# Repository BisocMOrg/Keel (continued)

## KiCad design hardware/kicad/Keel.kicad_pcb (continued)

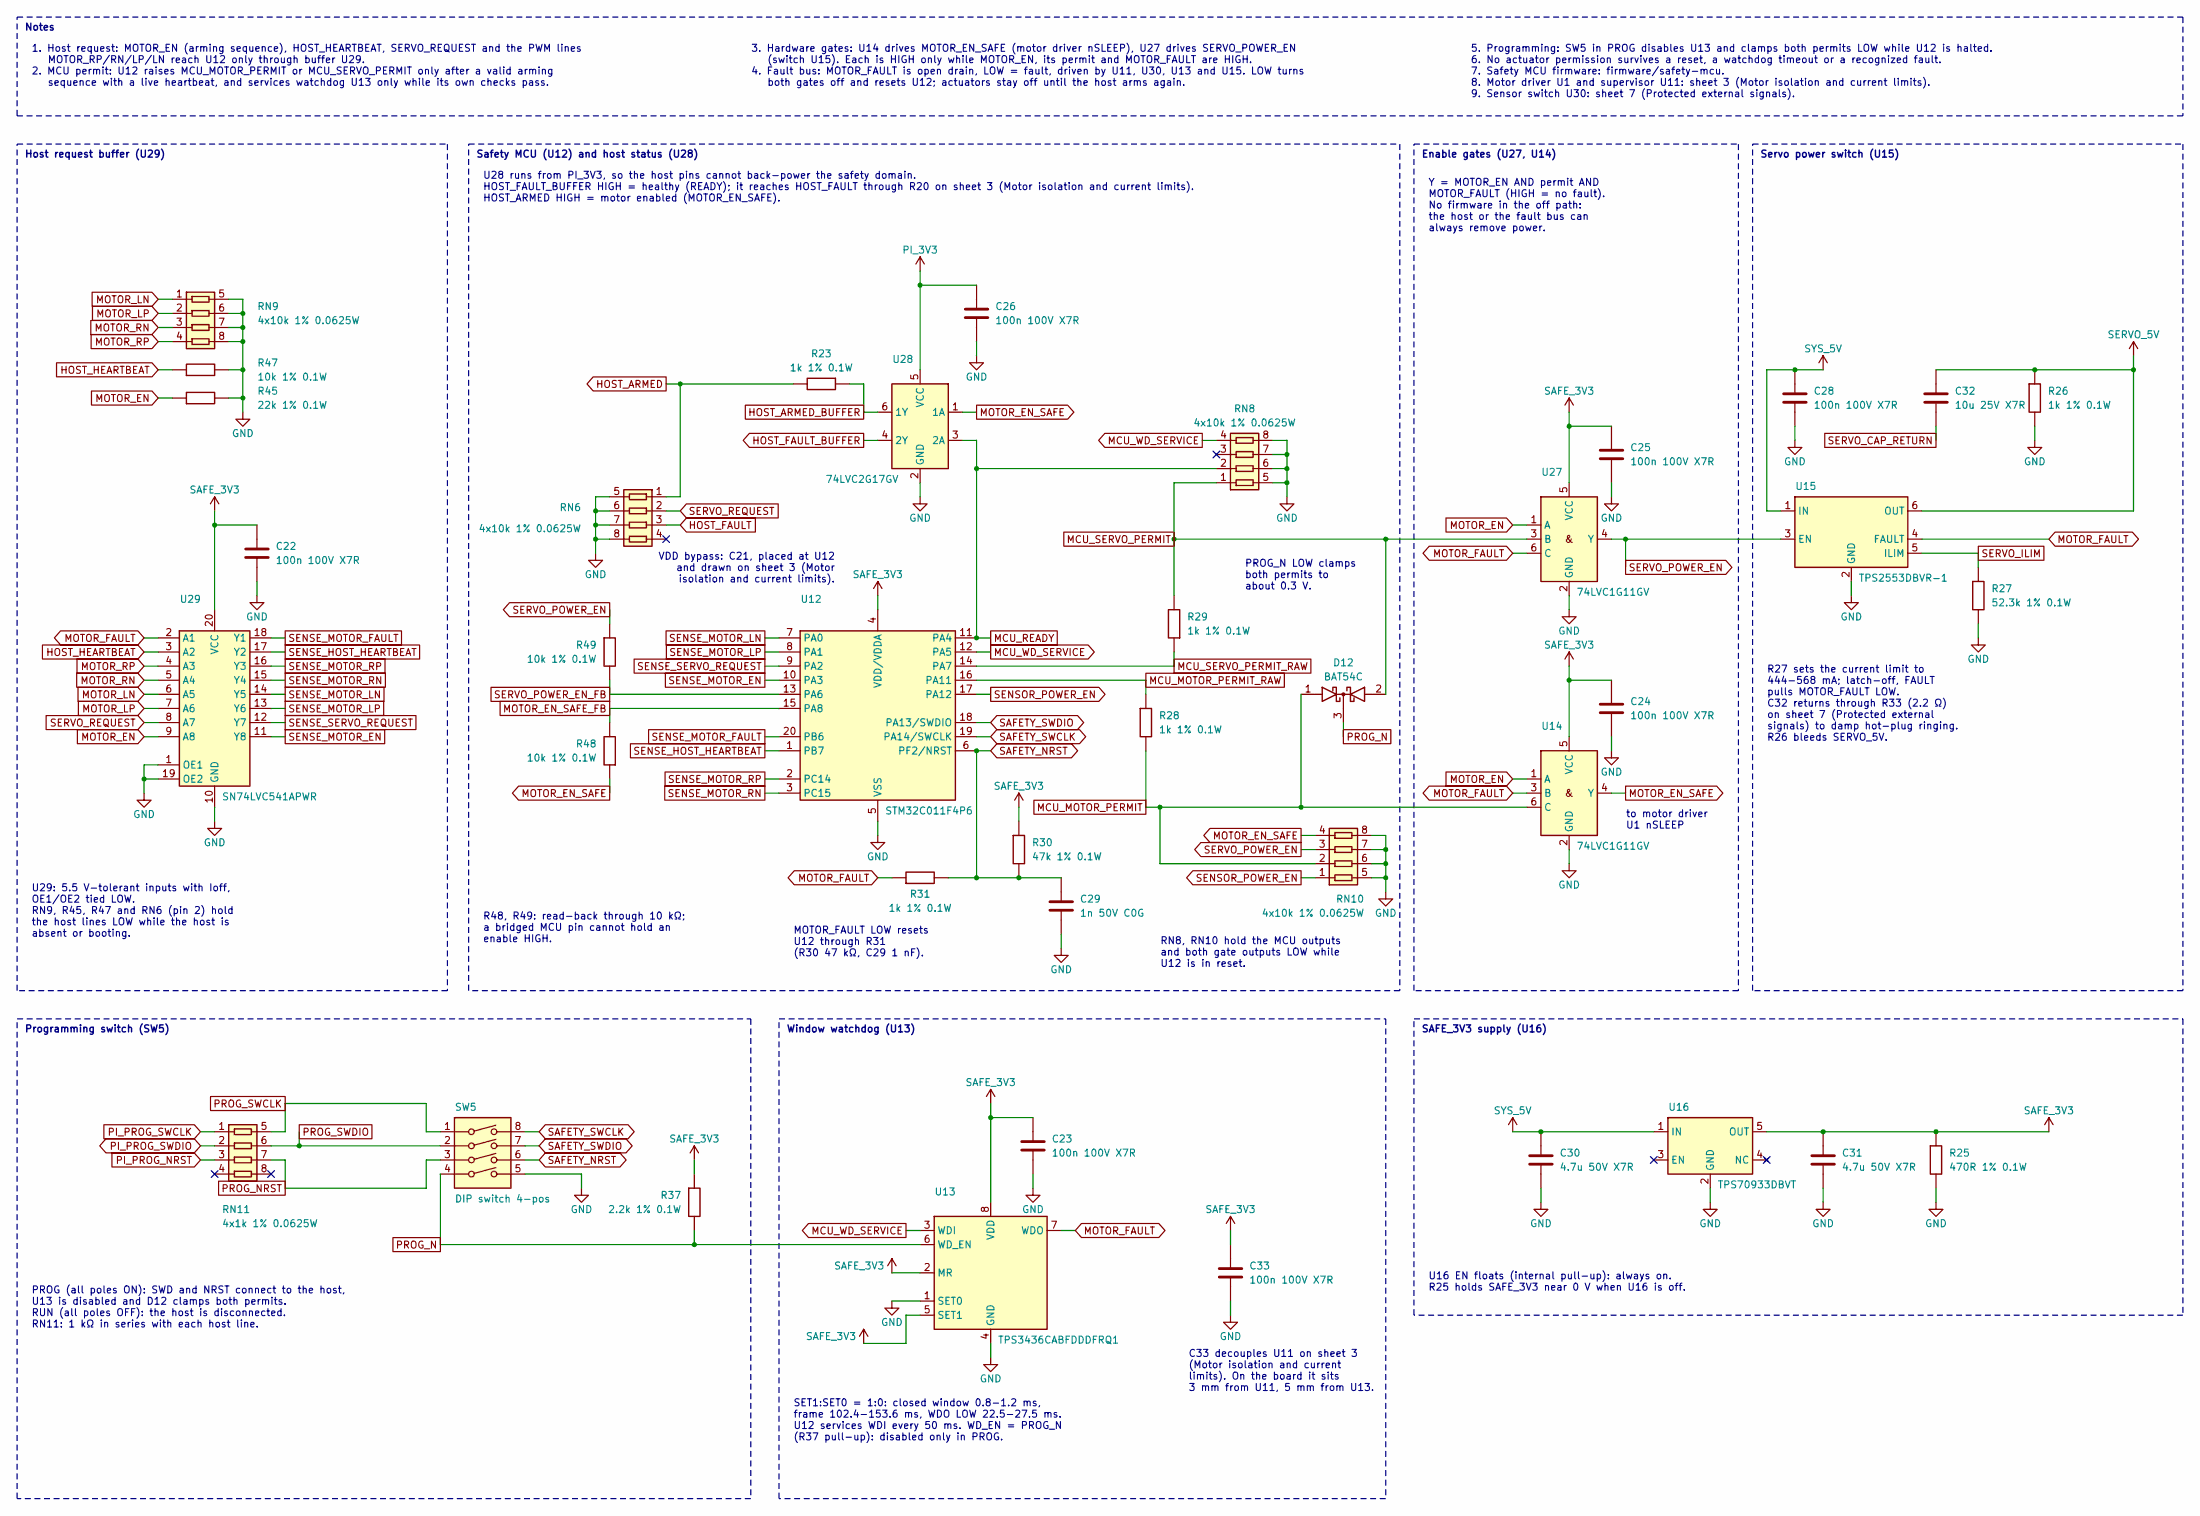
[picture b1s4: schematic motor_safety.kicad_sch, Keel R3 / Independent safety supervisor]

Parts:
C22, C23, C24, C25, C26, C28, C33: 100n 100V X7R; C_0603_1608Metric; MPN GRM188R72A104KA35D
C29: 1n 50V C0G; C_0603_1608Metric; MPN GRM1885C1H102JA01D
C30, C31: 4.7u 50V X7R; C_1206_3216Metric; MPN GRM31CR71H475KA12L
C32: 10u 25V X7R; C_1206_3216Metric; MPN GRM31CR71E106KA12L
D12: BAT54C; SOT-23; MPN BAT54C,215
R23, R26, R28, R29, R31: 1k 1% 0.1W; R_0603_1608Metric; MPN RC0603FR-071KL
R25: 470R 1% 0.1W; R_0603_1608Metric; MPN RC0603FR-07470RL
R27: 52.3k 1% 0.1W; R_0603_1608Metric; MPN RC0603FR-0752K3L
R30: 47k 1% 0.1W; R_0603_1608Metric; MPN RC0603FR-0747KL
R37: 2.2k 1% 0.1W; R_0603_1608Metric; MPN RC0603FR-072K2L
R45: 22k 1% 0.1W; R_0603_1608Metric; MPN RC0603FR-0722KL
R47, R48, R49: 10k 1% 0.1W; R_0603_1608Metric; MPN RC0603FR-0710KL
RN6, RN8, RN9, RN10: 4x10k 1% 0.0625W; YC164_4x0603; MPN YC164-FR-0710KL
RN11: 4x1k 1% 0.0625W; YC164_4x0603; MPN YC164-FR-071KL
SW5: DIP switch 4-pos; SW_DIP_SPSTx04_Slide_KingTek_DSHP04TS_W7.62mm_P1.27mm; MPN TDA04H0SB1R
U12: STM32C011F4P6; TSSOP-20_4.4x6.5mm_P0.65mm; MPN STM32C011F4P6
U13: TPS3436CABFDDDFRQ1; TI_DDF0008A_1.6x2.9mm_P0.65mm_CommonMask; MPN TPS3436CABFDDDFRQ1
U14, U27: 74LVC1G11GV; Nexperia_SOT457_SC74_1.5x2.9mm_P0.95mm; MPN 74LVC1G11GV,125
U15: TPS2553DBVR-1; SOT-23-6; MPN TPS2553DBVR-1
U16: TPS70933DBVT; SOT-23-5; MPN TPS70933DBVT
U28: 74LVC2G17GV; Nexperia_SOT457_SC74_1.5x2.9mm_P0.95mm; MPN 74LVC2G17GV,125
U29: SN74LVC541APWR; TSSOP-20_4.4x6.5mm_P0.65mm; MPN SN74LVC541APWR

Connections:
GND: C22.2, C23.2, C24.2, C25.2, C26.2, C28.2, C29.2, C30.2, C31.2, C33.2, R25.2, R26.2, R27.2, R45.2, R47.2, RN6.5, RN6.6, RN6.7, RN6.8, RN8.5, RN8.6, RN8.7, RN8.8, RN9.5, RN9.6, RN9.7, RN9.8, RN10.5, RN10.6, RN10.7, RN10.8, SW5.5 (S4), U12.5 (VSS), U13.1 (SET0), U13.4 (GND), U14.2 (GND), U15.2 (GND), U16.2 (GND), U27.2 (GND), U28.2 (GND), U29.1 (1OE), U29.10 (GND), U29.19 (2OE); also elsewhere on the board
HOST_ARMED: R23.2, RN6.1; also elsewhere on the board
HOST_ARMED_BUFFER: R23.1, U28.6 (1Y)
HOST_FAULT: RN6.3; also elsewhere on the board
HOST_FAULT_BUFFER: U28.4 (2Y); also elsewhere on the board
HOST_HEARTBEAT: R47.1, U29.3 (2Y4); also elsewhere on the board
MCU_MOTOR_PERMIT: D12.1 (A1), R28.2, RN10.2, U14.6 (C)
MCU_MOTOR_PERMIT_RAW: R28.1, U12.16 (PA11)
MCU_READY: RN8.2, U12.11 (PA4), U28.3 (2A)
MCU_SERVO_PERMIT: D12.2 (A2), R29.2, RN8.1, U27.3 (B)
MCU_SERVO_PERMIT_RAW: R29.1, U12.14 (PA7)
MCU_WD_SERVICE: RN8.4, U12.12 (PA5), U13.3 (WDI); also elsewhere on the board
MOTOR_EN: R45.1, U14.1 (A), U27.1 (A), U29.9 (2Y1); also elsewhere on the board
MOTOR_EN_SAFE: R48.1, RN10.4, U14.4 (Y), U28.1 (1A); also elsewhere on the board
MOTOR_EN_SAFE_FB: R48.2, U12.15 (PA8)
MOTOR_FAULT: R31.1, U13.7 (WDO), U14.3 (B), U15.4 (FAULT), U27.6 (C), U29.2 (1A1); also elsewhere on the board
MOTOR_LN: RN9.1, U29.6 (1A3); also elsewhere on the board
MOTOR_LP: RN9.2, U29.7 (2Y2); also elsewhere on the board
MOTOR_RN: RN9.3, U29.5 (2Y3); also elsewhere on the board
MOTOR_RP: RN9.4, U29.4 (1A2); also elsewhere on the board
PI_3V3: C26.1, U28.5 (VCC); also elsewhere on the board
PI_PROG_NRST: RN11.3; also elsewhere on the board
PI_PROG_SWCLK: RN11.1; also elsewhere on the board
PI_PROG_SWDIO: RN11.2; also elsewhere on the board
PROG_N: D12.3 (K), R37.2, SW5.4 (S4), U13.6 (WD_EN)
PROG_NRST: RN11.7, SW5.3 (S3)
PROG_SWCLK: RN11.5, SW5.1 (S1)
PROG_SWDIO: RN11.6, SW5.2 (S2)
SAFETY_NRST: C29.1, R30.2, R31.2, SW5.6 (S3), U12.6 (PF2/NRST); also elsewhere on the board
SAFETY_SWCLK: SW5.8 (S1), U12.19 (PA14/SWCLK); also elsewhere on the board
SAFETY_SWDIO: SW5.7 (S2), U12.18 (PA13/SWDIO); also elsewhere on the board
SAFE_3V3: C22.1, C23.1, C24.1, C25.1, C31.1, C33.1, R25.1, R30.1, R37.1, U12.4 (VDD/VDDA), U13.2 (MR), U13.5 (SET1), U13.8 (VDD), U14.5 (VCC), U16.5 (OUT), U27.5 (VCC), U29.20 (VCC); also elsewhere on the board
SENSE_HOST_HEARTBEAT: U12.1 (PB7), U29.17 (2A4)
SENSE_MOTOR_EN: U12.10 (PA3), U29.11 (2A1)
SENSE_MOTOR_FAULT: U12.20 (PB6), U29.18 (1Y1)
SENSE_MOTOR_LN: U12.7 (PA0), U29.14 (1Y3)
SENSE_MOTOR_LP: U12.8 (PA1), U29.13 (2A2)
SENSE_MOTOR_RN: U12.3 (PC15), U29.15 (2A3)
SENSE_MOTOR_RP: U12.2 (PC14), U29.16 (1Y2)
SENSE_SERVO_REQUEST: U12.9 (PA2), U29.12 (1Y4)
SENSOR_POWER_EN: RN10.1, U12.17 (PA12); also elsewhere on the board
SERVO_5V: C32.1, R26.1, U15.6 (OUT); also elsewhere on the board
SERVO_CAP_RETURN: C32.2; also elsewhere on the board
SERVO_ILIM: R27.1, U15.5 (ILIM)
SERVO_POWER_EN: R49.1, RN10.3, U15.3 (EN), U27.4 (Y); also elsewhere on the board
SERVO_POWER_EN_FB: R49.2, U12.13 (PA6)
SERVO_REQUEST: RN6.2, U29.8 (1A4); also elsewhere on the board
SYS_5V: C28.1, C30.1, U15.1 (IN), U16.1 (IN); also elsewhere on the board

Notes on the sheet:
VDD bypass: C21, placed at U12 and drawn on sheet 3 (Motor isolation and current limits).
to motor driver U1 nSLEEP
Host request buffer (U29)
Safety MCU (U12) and host status (U28)
Enable gates (U27, U14)
Servo power switch (U15)
Programming switch (SW5)
Window watchdog (U13)
SAFE_3V3 supply (U16)
Notes
1. Host request: MOTOR_EN (arming sequence), HOST_HEARTBEAT, SERVO_REQUEST and the PWM lines MOTOR_RP/RN/LP/LN reach U12 only through buffer U29. 2. MCU permit: U12 raises MCU_MOTOR_PERMIT or MCU_SERVO_PERMIT only after a valid arming sequence with a live heartbeat, and services watchdog U13 only w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
3. Hardware gates: U14 drives MOTOR_EN_SAFE (motor driver nSLEEP), U27 drives SERVO_POWER_EN (switch U15). Each is HIGH only while MOTOR_EN, its permit and MOTOR_FAULT are HIGH. 4. Fault bus: MOTOR_FAULT is open drain, LOW = fault, driven by U11, U30, U13 and U15. LOW turns both gates off and reset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
5. Programming: SW5 in PROG disables U13 and clamps both permits LOW while U12 is halted. 6. No actuator permission survives a reset, a watchdog timeout or a recognized fault. 7. Safety MCU firmware: firmware/safety-mcu. 8. Motor driver U1 and supervisor U11: sheet 3 (Motor isolation and current li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
U29: 5.5 V-tolerant inputs with Ioff, OE1/OE2 tied LOW. RN9, R45, R47 and RN6 (pin 2) hold the host lines LOW while the host is absent or booting.
U28 runs from PI_3V3, so the host pins cannot back-power the safety domain. HOST_FAULT_BUFFER HIGH = healthy (READY); it reaches HOST_FAULT through R20 on sheet 3 (Motor isolation and current limits). HOST_ARMED HIGH = motor enabled (MOTOR_EN_SAFE).
R48, R49: read-back through 10 kΩ; a bridged MCU pin cannot hold an enable HIGH.
MOTOR_FAULT LOW resets U12 through R31 (R30 47 kΩ, C29 1 nF).
PROG_N LOW clamps both permits to about 0.3 V.
RN8, RN10 hold the MCU outputs and both gate outputs LOW while U12 is in reset.
Y = MOTOR_EN AND permit AND MOTOR_FAULT (HIGH = no fault). No firmware in the off path: the host or the fault bus can always remove power.
R27 sets the current limit to 444-568 mA; latch-off, FAULT pulls MOTOR_FAULT LOW. C32 returns through R33 (2.2 Ω) on sheet 7 (Protected external signals) to damp hot-plug ringing. R26 bleeds SERVO_5V.
PROG (all poles ON): SWD and NRST connect to the host, U13 is disabled and D12 clamps both permits. RUN (all poles OFF): the host is disconnected. RN11: 1 kΩ in series with each host line.
SET1:SET0 = 1:0: closed window 0.8-1.2 ms, frame 102.4-153.6 ms, WDO LOW 22.5-27.5 ms. U12 services WDI every 50 ms. WD_EN = PROG_N (R37 pull-up): disabled only in PROG.
C33 decouples U11 on sheet 3 (Motor isolation and current limits). On the board it sits 3 mm from U11, 5 mm from U13.
U16 EN floats (internal pull-up): always on. R25 holds SAFE_3V3 near 0 V when U16 is off.

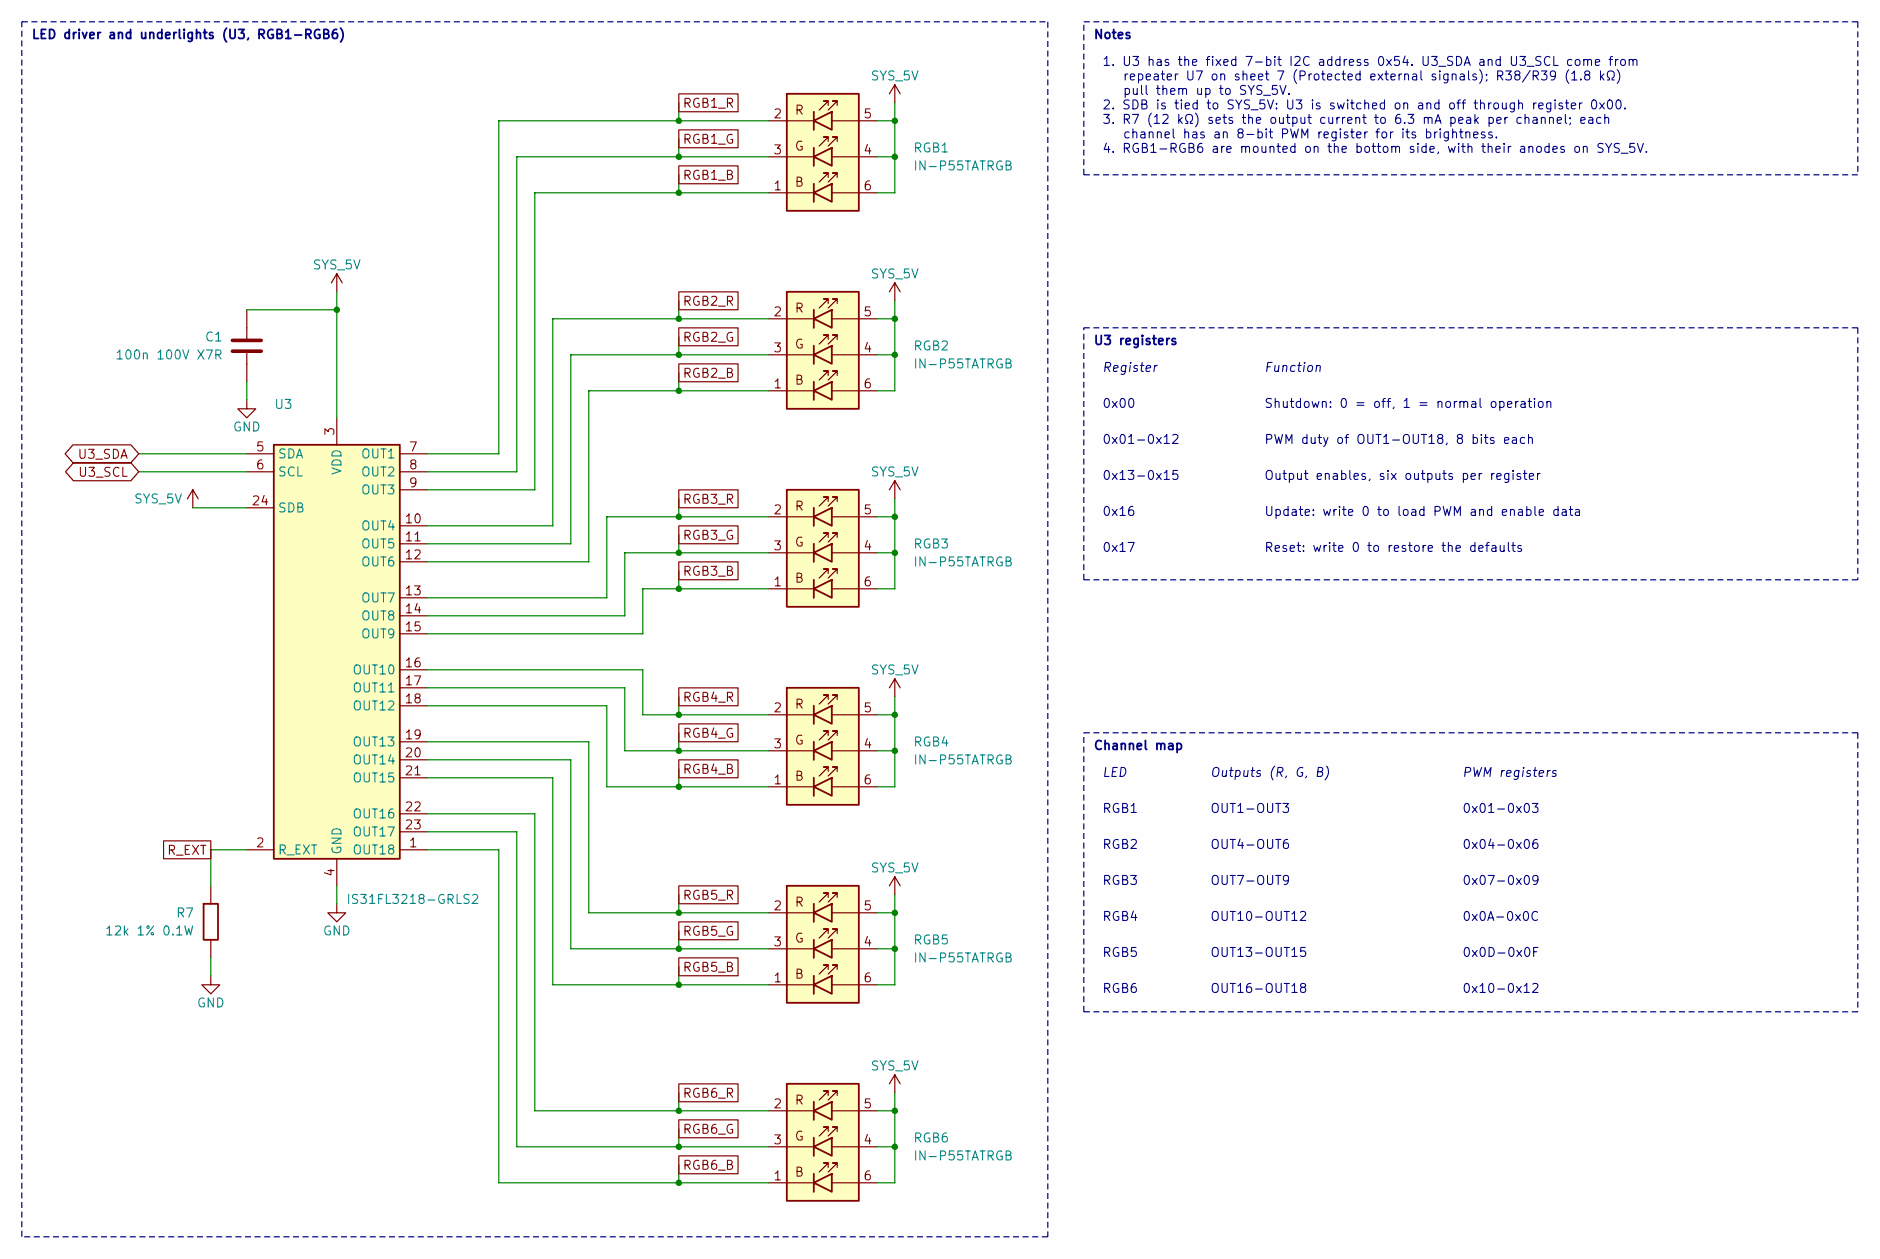
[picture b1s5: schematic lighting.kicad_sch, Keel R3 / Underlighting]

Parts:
C1: 100n 100V X7R; C_0603_1608Metric; MPN GRM188R72A104KA35D
R7: 12k 1% 0.1W; R_0603_1608Metric; MPN RC0603FR-0712KL
RGB1, RGB2, RGB3, RGB4, RGB5, RGB6: IN-P55TATRGB; LED_Inolux_IN-P55TATRGB_PLCC6_5.0x5.5mm_P1.8mm; MPN IN-P55TATRGB
U3: IS31FL3218-GRLS2; IS31FL3218_SOP24; MPN IS31FL3218-GRLS2

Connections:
GND: C1.2, R7.2, U3.4 (GND); also elsewhere on the board
RGB1_B: RGB1.1 (BC), U3.9 (OUT3)
RGB1_G: RGB1.3 (GC), U3.8 (OUT2)
RGB1_R: RGB1.2 (RC), U3.7 (OUT1)
RGB2_B: RGB2.1 (BC), U3.12 (OUT6)
RGB2_G: RGB2.3 (GC), U3.11 (OUT5)
RGB2_R: RGB2.2 (RC), U3.10 (OUT4)
RGB3_B: RGB3.1 (BC), U3.15 (OUT9)
RGB3_G: RGB3.3 (GC), U3.14 (OUT8)
RGB3_R: RGB3.2 (RC), U3.13 (OUT7)
RGB4_B: RGB4.1 (BC), U3.18 (OUT12)
RGB4_G: RGB4.3 (GC), U3.17 (OUT11)
RGB4_R: RGB4.2 (RC), U3.16 (OUT10)
RGB5_B: RGB5.1 (BC), U3.21 (OUT15)
RGB5_G: RGB5.3 (GC), U3.20 (OUT14)
RGB5_R: RGB5.2 (RC), U3.19 (OUT13)
RGB6_B: RGB6.1 (BC), U3.1 (OUT18)
RGB6_G: RGB6.3 (GC), U3.23 (OUT17)
RGB6_R: RGB6.2 (RC), U3.22 (OUT16)
R_EXT: R7.1, U3.2 (R_EXT)
SYS_5V: C1.1, RGB1.4 (GA), RGB1.5 (RA), RGB1.6 (BA), RGB2.4 (GA), RGB2.5 (RA), RGB2.6 (BA), RGB3.4 (GA), RGB3.5 (RA), RGB3.6 (BA), RGB4.4 (GA), RGB4.5 (RA), RGB4.6 (BA), RGB5.4 (GA), RGB5.5 (RA), RGB5.6 (BA), RGB6.4 (GA), RGB6.5 (RA), RGB6.6 (BA), U3.3 (VDD), U3.24 (SDB); also elsewhere on the board
U3_SCL: U3.6 (SCL); also elsewhere on the board
U3_SDA: U3.5 (SDA); also elsewhere on the board

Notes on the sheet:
LED driver and underlights (U3, RGB1-RGB6)
Notes
1. U3 has the fixed 7-bit I2C address 0x54. U3_SDA and U3_SCL come from repeater U7 on sheet 7 (Protected external signals); R38/R39 (1.8 kΩ) pull them up to SYS_5V. 2. SDB is tied to SYS_5V: U3 is switched on and off through register 0x00. 3. R7 (12 kΩ) sets the output current to 6.3 mA peak per c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
U3 registers
Register
Function
0x00
Shutdown: 0 = off, 1 = normal operation
0x01-0x12
PWM duty of OUT1-OUT18, 8 bits each
0x13-0x15
Output enables, six outputs per register
0x16
Update: write 0 to load PWM and enable data
0x17
Reset: write 0 to restore the defaults
Channel map
LED
Outputs (R, G, B)
PWM registers
RGB1
OUT1-OUT3
0x01-0x03
RGB2
OUT4-OUT6
0x04-0x06
RGB3
OUT7-OUT9
0x07-0x09
RGB4
OUT10-OUT12
0x0A-0x0C
RGB5
OUT13-OUT15
0x0D-0x0F
RGB6
OUT16-OUT18
0x10-0x12

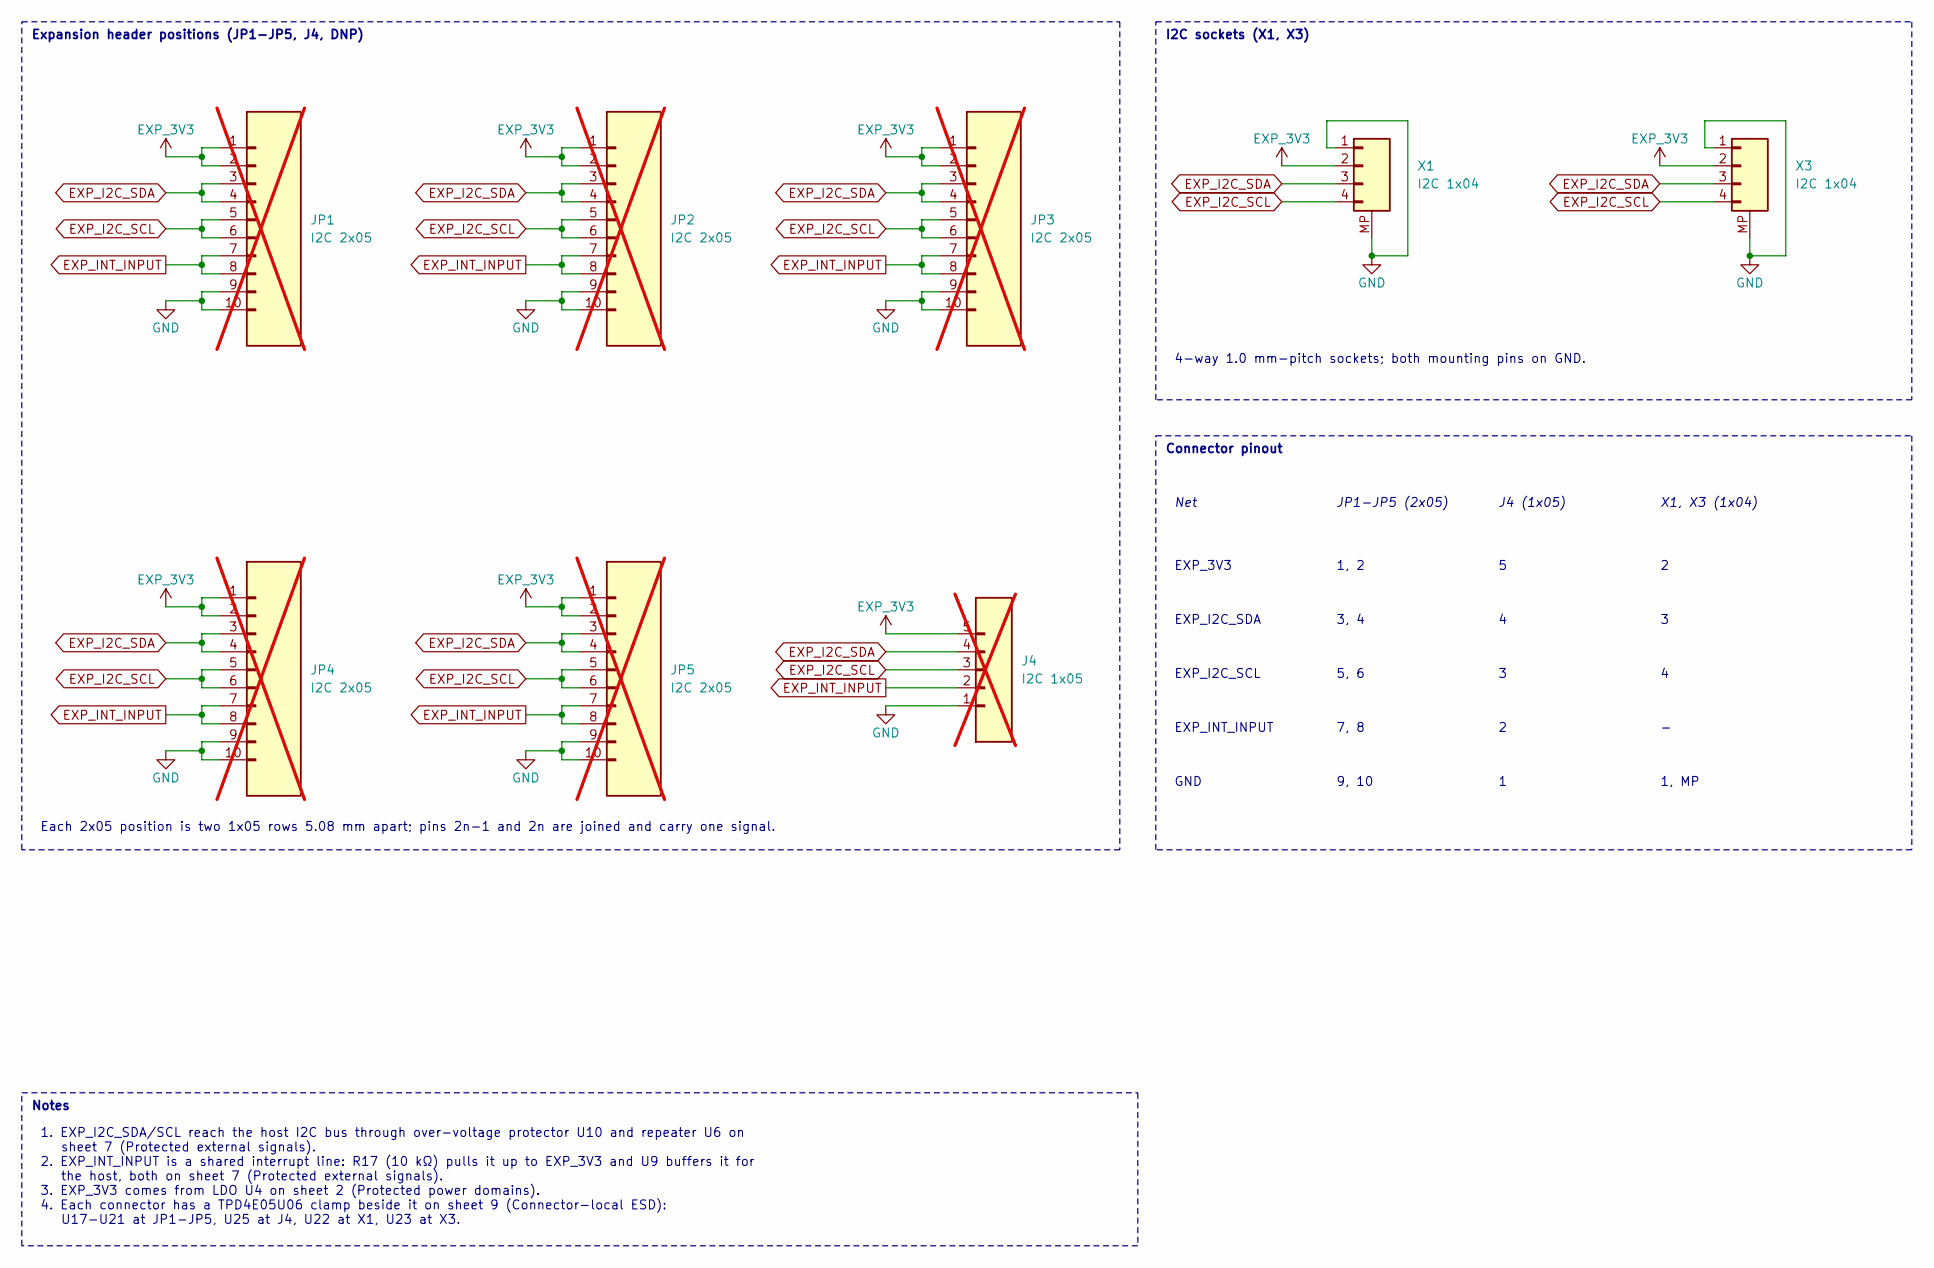
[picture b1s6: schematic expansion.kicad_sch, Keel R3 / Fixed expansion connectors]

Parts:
J4: I2C 1x05; PinHeader_1x05_P2.54mm_Vertical; not fitted
JP1, JP2, JP3, JP4, JP5: I2C 2x05; PinHeader_2x05_Row5.08_DNP; not fitted
X1, X3: I2C 1x04; JST_SH_BM04B-SRSS-TB_1x04-1MP_P1.00mm_Vertical; MPN BM04B-SRSS-TB

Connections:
EXP_3V3: J4.5, JP1.1, JP1.2, JP2.1, JP2.2, JP3.1, JP3.2, JP4.1, JP4.2, JP5.1, JP5.2, X1.2, X3.2; also elsewhere on the board
EXP_I2C_SCL: J4.3, JP1.5, JP1.6, JP2.5, JP2.6, JP3.5, JP3.6, JP4.5, JP4.6, JP5.5, JP5.6, X1.4, X3.4; also elsewhere on the board
EXP_I2C_SDA: J4.4, JP1.3, JP1.4, JP2.3, JP2.4, JP3.3, JP3.4, JP4.3, JP4.4, JP5.3, JP5.4, X1.3, X3.3; also elsewhere on the board
EXP_INT_INPUT: J4.2, JP1.7, JP1.8, JP2.7, JP2.8, JP3.7, JP3.8, JP4.7, JP4.8, JP5.7, JP5.8; also elsewhere on the board
GND: J4.1, JP1.9, JP1.10, JP2.9, JP2.10, JP3.9, JP3.10, JP4.9, JP4.10, JP5.9, JP5.10, X1.1, X1.MP (mounts), X3.1, X3.MP (mounts); also elsewhere on the board

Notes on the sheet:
Expansion header positions (JP1-JP5, J4, DNP)
Each 2x05 position is two 1x05 rows 5.08 mm apart; pins 2n-1 and 2n are joined and carry one signal.
I2C sockets (X1, X3)
4-way 1.0 mm-pitch sockets; both mounting pins on GND.
Connector pinout
Net
JP1-JP5 (2x05)
J4 (1x05)
X1, X3 (1x04)
EXP_3V3
1, 2
EXP_I2C_SDA
3, 4
EXP_I2C_SCL
5, 6
EXP_INT_INPUT
7, 8
GND
9, 10
1, MP
Notes
1. EXP_I2C_SDA/SCL reach the host I2C bus through over-voltage protector U10 and repeater U6 on sheet 7 (Protected external signals). 2. EXP_INT_INPUT is a shared interrupt line: R17 (10 kΩ) pulls it up to EXP_3V3 and U9 buffers it for the host, both on sheet 7 (Protected external signals). 3. EXP_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

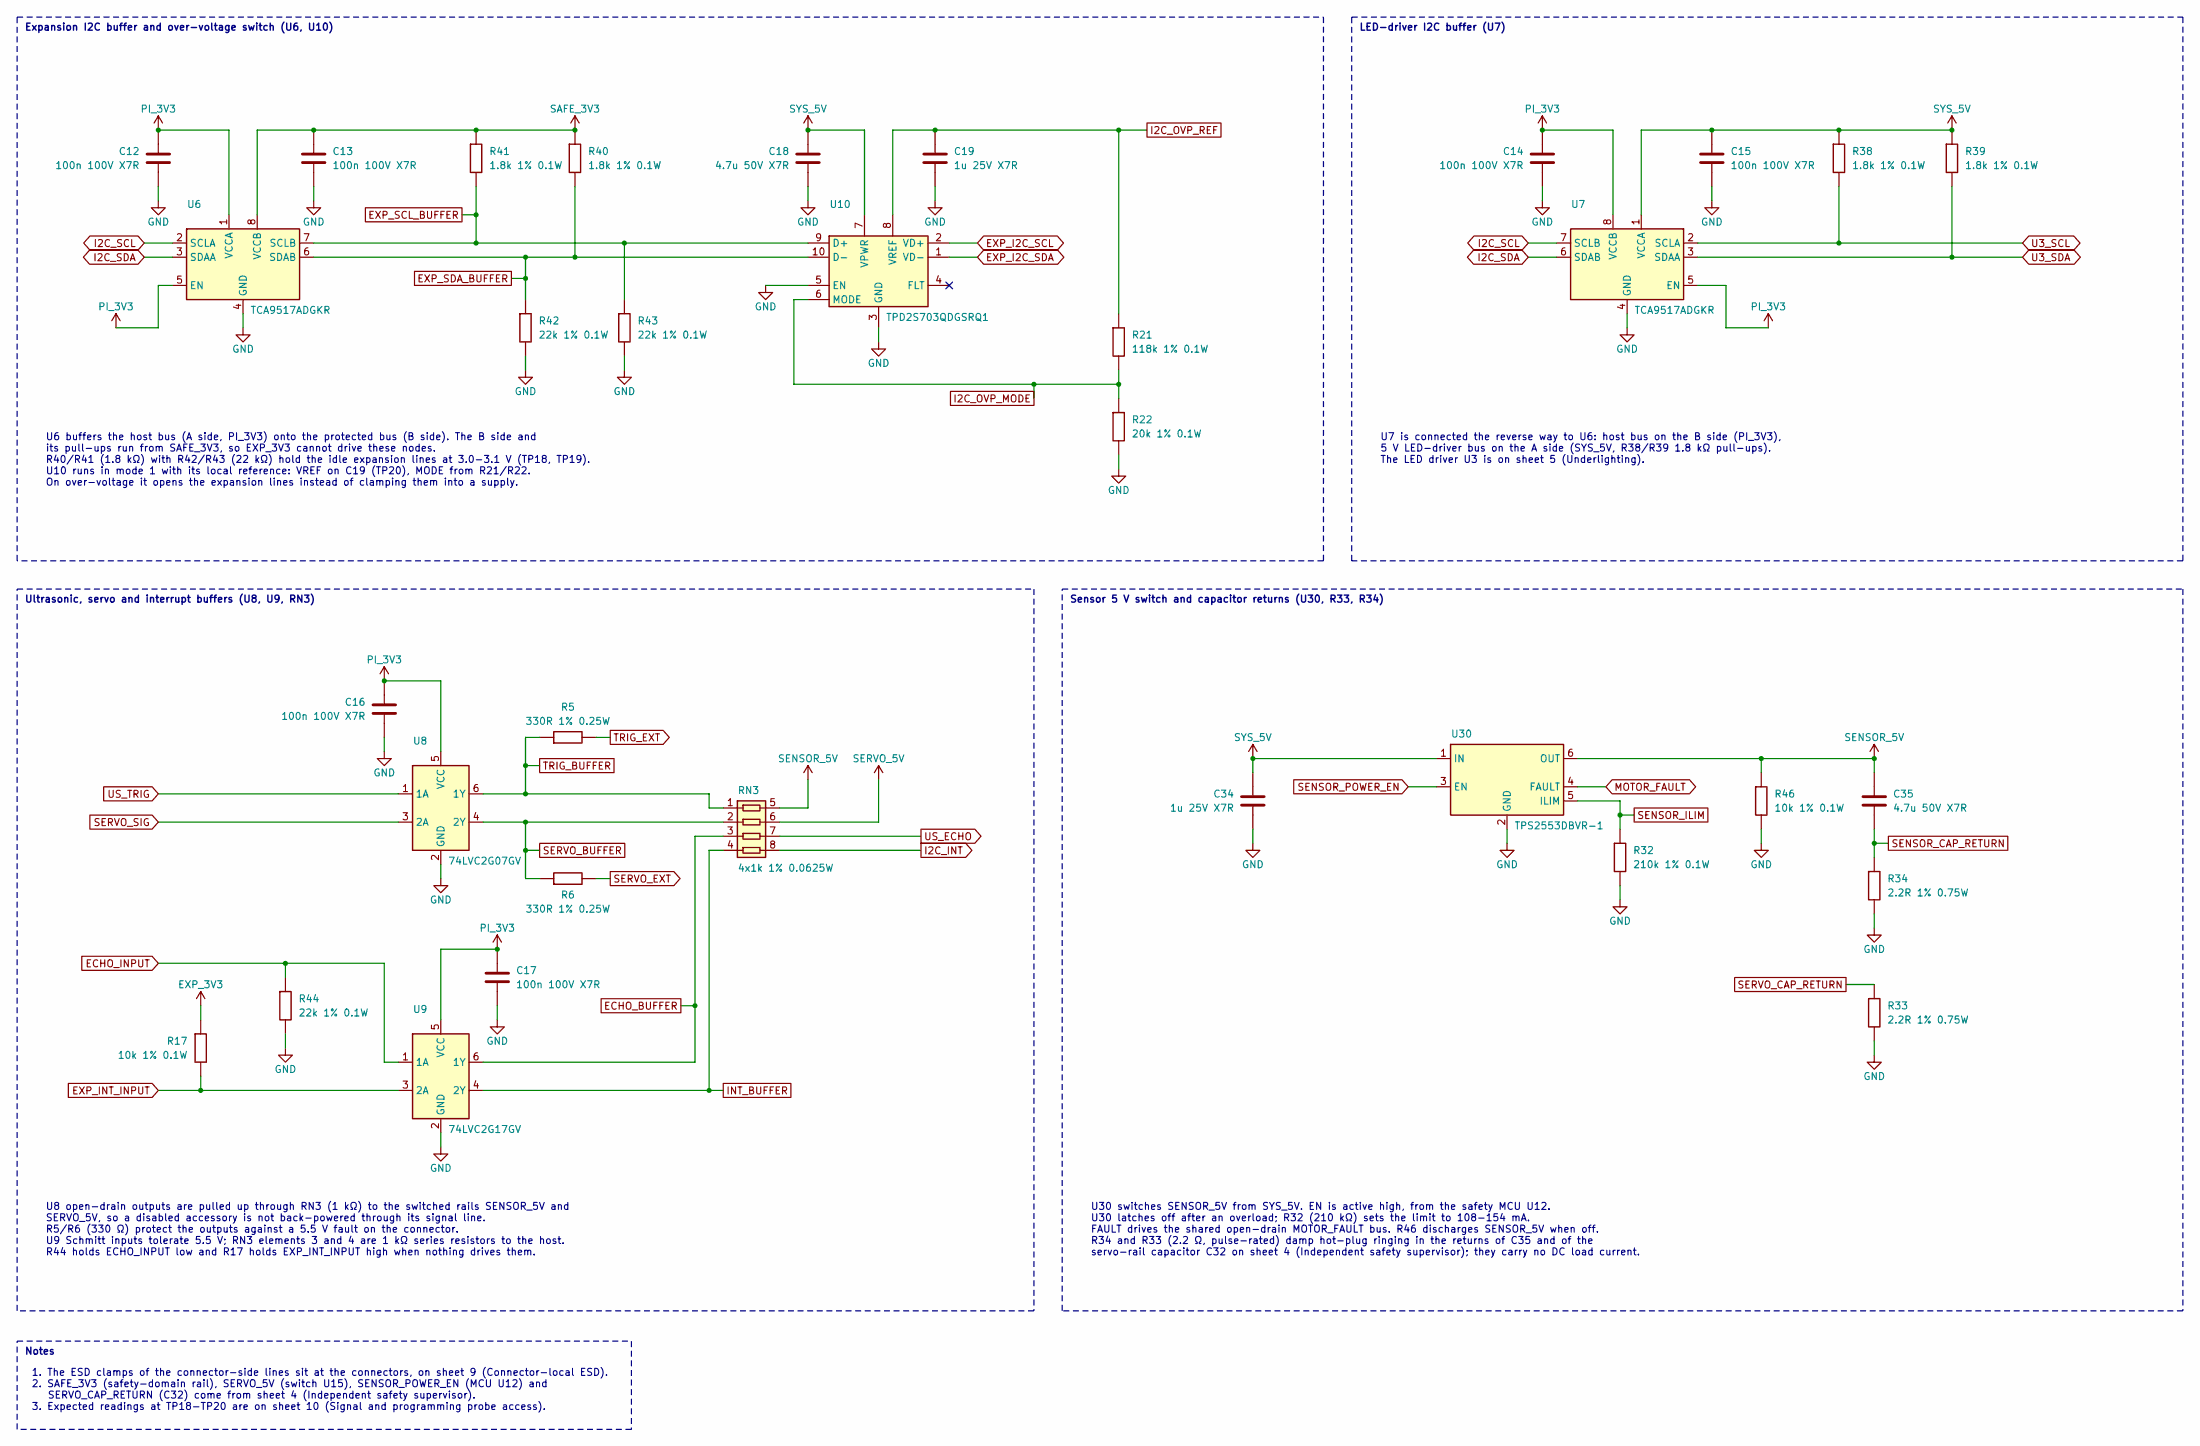
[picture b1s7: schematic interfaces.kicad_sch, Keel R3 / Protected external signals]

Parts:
C12, C13, C14, C15, C16, C17: 100n 100V X7R; C_0603_1608Metric; MPN GRM188R72A104KA35D
C18, C35: 4.7u 50V X7R; C_1206_3216Metric; MPN GRM31CR71H475KA12L
C19, C34: 1u 25V X7R; C_0805_2012Metric; MPN GRM219R71E105KA88D
R5, R6: 330R 1% 0.25W; R_1206_3216Metric; MPN RC1206FR-07330RL
R17, R46: 10k 1% 0.1W; R_0603_1608Metric; MPN RC0603FR-0710KL
R21: 118k 1% 0.1W; R_0603_1608Metric; MPN RC0603FR-07118KL
R22: 20k 1% 0.1W; R_0603_1608Metric; MPN RC0603FR-0720KL
R32: 210k 1% 0.1W; R_0603_1608Metric; MPN RC0603FR-07210KL
R33, R34: 2.2R 1% 0.75W; R_1206_3216Metric; MPN CRCW12062R20FKEAHP
R38, R39, R40, R41: 1.8k 1% 0.1W; R_0603_1608Metric; MPN RC0603FR-071K8L
R42, R43, R44: 22k 1% 0.1W; R_0603_1608Metric; MPN RC0603FR-0722KL
RN3: 4x1k 1% 0.0625W; YC164_4x0603; MPN YC164-FR-071KL
U6, U7: TCA9517ADGKR; VSSOP-8_3x3mm_P0.65mm; MPN TCA9517ADGKR
U8: 74LVC2G07GV; Nexperia_SOT457_SC74_1.5x2.9mm_P0.95mm; MPN 74LVC2G07GV,125
U9: 74LVC2G17GV; Nexperia_SOT457_SC74_1.5x2.9mm_P0.95mm; MPN 74LVC2G17GV,125
U10: TPD2S703QDGSRQ1; MSOP-10_3x3mm_P0.5mm; MPN TPD2S703QDGSRQ1
U30: TPS2553DBVR-1; SOT-23-6; MPN TPS2553DBVR-1

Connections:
ECHO_BUFFER: RN3.3, U9.6 (1Y)
ECHO_INPUT: R44.1, U9.1 (1A); also elsewhere on the board
EXP_3V3: R17.1; also elsewhere on the board
EXP_I2C_SCL: U10.2 (VD+); also elsewhere on the board
EXP_I2C_SDA: U10.1 (VD-); also elsewhere on the board
EXP_INT_INPUT: R17.2, U9.3 (2A); also elsewhere on the board
EXP_SCL_BUFFER: R41.2, R43.1, U6.7 (SCLB), U10.9 (D+)
EXP_SDA_BUFFER: R40.2, R42.1, U6.6 (SDAB), U10.10 (D-)
GND: C12.2, C13.2, C14.2, C15.2, C16.2, C17.2, C18.2, C19.2, C34.2, R22.2, R32.2, R33.2, R34.2, R42.2, R43.2, R44.2, R46.2, U6.4 (GND), U7.4 (GND), U8.2 (GND), U9.2 (GND), U10.3 (GND), U10.5 (EN), U30.2 (GND); also elsewhere on the board
I2C_INT: RN3.8; also elsewhere on the board
I2C_OVP_MODE: R21.2, R22.1, U10.6 (MODE)
I2C_OVP_REF: C19.1, R21.1, U10.8 (VREF); also elsewhere on the board
I2C_SCL: U6.2 (SCLA), U7.7 (SCLB); also elsewhere on the board
I2C_SDA: U6.3 (SDAA), U7.6 (SDAB); also elsewhere on the board
INT_BUFFER: RN3.4, U9.4 (2Y)
MOTOR_FAULT: U30.4 (FAULT); also elsewhere on the board
PI_3V3: C12.1, C14.1, C16.1, C17.1, U6.1 (VCCA), U6.5 (EN), U7.5 (EN), U7.8 (VCCB), U8.5 (VCC), U9.5 (VCC); also elsewhere on the board
SAFE_3V3: C13.1, R40.1, R41.1, U6.8 (VCCB); also elsewhere on the board
SENSOR_5V: C35.1, R46.1, RN3.5, U30.6 (OUT); also elsewhere on the board
SENSOR_CAP_RETURN: C35.2, R34.1
SENSOR_ILIM: R32.1, U30.5 (ILIM)
SENSOR_POWER_EN: U30.3 (EN); also elsewhere on the board
SERVO_5V: RN3.6; also elsewhere on the board
SERVO_BUFFER: R6.1, RN3.2, U8.4 (2Y)
SERVO_CAP_RETURN: R33.1; also elsewhere on the board
SERVO_EXT: R6.2; also elsewhere on the board
SERVO_SIG: U8.3 (2A); also elsewhere on the board
SYS_5V: C15.1, C18.1, C34.1, R38.1, R39.1, U7.1 (VCCA), U10.7 (VPWR), U30.1 (IN); also elsewhere on the board
TRIG_BUFFER: R5.1, RN3.1, U8.6 (1Y)
TRIG_EXT: R5.2; also elsewhere on the board
U3_SCL: R38.2, U7.2 (SCLA); also elsewhere on the board
U3_SDA: R39.2, U7.3 (SDAA); also elsewhere on the board
US_ECHO: RN3.7; also elsewhere on the board
US_TRIG: U8.1 (1A); also elsewhere on the board

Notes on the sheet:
U6 buffers the host bus (A side, PI_3V3) onto the protected bus (B side). The B side and its pull-ups run from SAFE_3V3, so EXP_3V3 cannot drive these nodes. R40/R41 (1.8 kΩ) with R42/R43 (22 kΩ) hold the idle expansion lines at 3.0-3.1 V (TP18, TP19). U10 runs in mode 1 with its local reference: V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
Expansion I2C buffer and over-voltage switch (U6, U10)
U7 is connected the reverse way to U6: host bus on the B side (PI_3V3), 5 V LED-driver bus on the A side (SYS_5V, R38/R39 1.8 kΩ pull-ups). The LED driver U3 is on sheet 5 (Underlighting).
LED-driver I2C buffer (U7)
U8 open-drain outputs are pulled up through RN3 (1 kΩ) to the switched rails SENSOR_5V and SERVO_5V, so a disabled accessory is not back-powered through its signal line. R5/R6 (330 Ω) protect the outputs against a 5.5 V fault on the connector. U9 Schmitt inputs tolerate 5.5 V; RN3 elements 3 and 4 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
Ultrasonic, servo and interrupt buffers (U8, U9, RN3)
U30 switches SENSOR_5V from SYS_5V. EN is active high, from the safety MCU U12. U30 latches off after an overload; R32 (210 kΩ) sets the limit to 108-154 mA. FAULT drives the shared open-drain MOTOR_FAULT bus. R46 discharges SENSOR_5V when off. R34 and R33 (2.2 Ω, pulse-rated) damp hot-plug ringing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
Sensor 5 V switch and capacitor returns (U30, R33, R34)
Notes
1. The ESD clamps of the connector-side lines sit at the connectors, on sheet 9 (Connector-local ESD). 2. SAFE_3V3 (safety-domain rail), SERVO_5V (switch U15), SENSOR_POWER_EN (MCU U12) and SERVO_CAP_RETURN (C32) come from sheet 4 (Independent safety supervisor). 3. Expected readings at TP18-TP20 a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
